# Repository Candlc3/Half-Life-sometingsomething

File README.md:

# Half-Life-sometingsomething
This is for that 10 week project that I will lock in on

there are two versions. One with and one without a battery. Reviewer, please look at v2 first because i would like to build it with a battery. 

IF for some reason v2 doesn't work, just check v1, as its the same thing but with an extra rotary encoder. 

I'm pretty sure the code for both is the same one just uses a battery. 

heres a cool screenshot of what i did for my starbieV1 (its a rock)

V2 just has a big battery at the top.

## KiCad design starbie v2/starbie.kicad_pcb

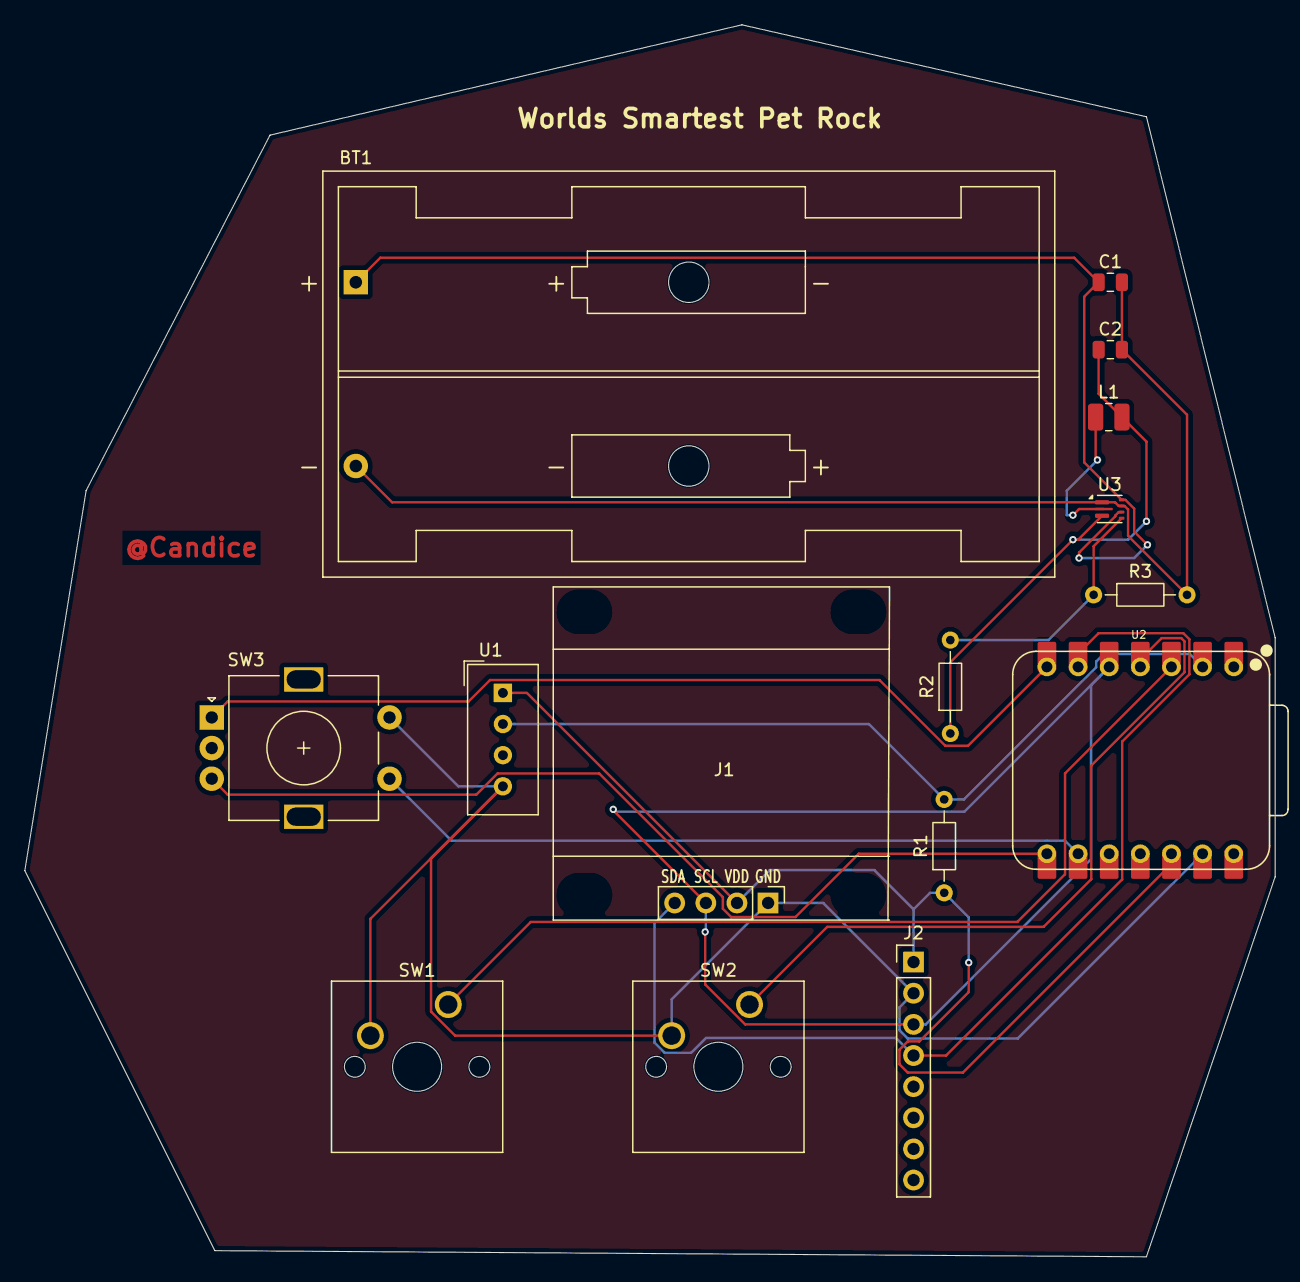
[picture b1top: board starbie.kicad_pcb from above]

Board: 2 copper layers, 102.0 x 100.5 mm, 15 parts (0 on the bottom side), 15 nets.

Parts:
BT1: Battery; BatteryHolder_Keystone_2462_2xAA
C1: 10uF 6.3V X5R; C_0805_2012Metric
C2: C; C_0805_2012Metric
J1: Conn_01x04_Pin; Display_128x64_096_I2C
J2: Conn_01x08_Pin; PinHeader_1x08_P2.54mm_Vertical
L1: 4.7uH 3A; L_1008_2520Metric
R1: 10k; R_Axial_DIN0204_L3.6mm_D1.6mm_P7.62mm_Horizontal
R2: 470kΩ; R_Axial_DIN0204_L3.6mm_D1.6mm_P7.62mm_Horizontal
R3: 56kΩ; R_Axial_DIN0204_L3.6mm_D1.6mm_P7.62mm_Horizontal
SW1, SW2: SW_Push; SW_Cherry_MX_1.00u_PCB
SW3: RotaryEncoder_Switch; RotaryEncoder_Alps_EC11E-Switch_Vertical_H20mm
U1: DHT11; Aosong_DHT11_5.5x12.0_P2.54mm
U2: XIAO-ESP32-C3-SMD; XIAO-ESP32-C6-DIP
U3: TPS61022; Texas_RWU0007A_VQFN-7_2x2mm_P0.5mm

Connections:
+3.3V: J1.2, J2.1, R1.1, U1.1 (VDD), U2.12 (3V3_OUT)
/DHT11 DATA: R1.2, U1.2 (DATA), U2.2 (D1)
/GPIO2: SW1.1, U2.3 (D2)
/GPIO3: SW2.1, U2.4 (D3)
/SCL: J1.3, J2.3, U2.5 (D4)
/SDA: J1.4, J2.4, U2.6 (D5)
/true gnd: BT1.2 (-), C1.2, C2.2, R3.2, U3.1 (GND), U3.6 (MODE)
GND: J1.1, J2.2, SW1.2, SW2.2, SW3.S2, U1.4 (GND), U2.13 (GND)
unnamed: BT1.1 (+), C1.1, U3.5 (EN), U3.7 (VIN)
unnamed: SW3.A, U2.7 (D6)
unnamed: SW3.B, U2.8 (D7)
unnamed: SW3.S1, U2.9 (D8)
unnamed: R2.2, R3.1, U3.4 (FB)
unnamed: L1.1, U3.2 (SW)
unnamed: C2.1, L1.2, R2.1, U3.3 (VOUT)
